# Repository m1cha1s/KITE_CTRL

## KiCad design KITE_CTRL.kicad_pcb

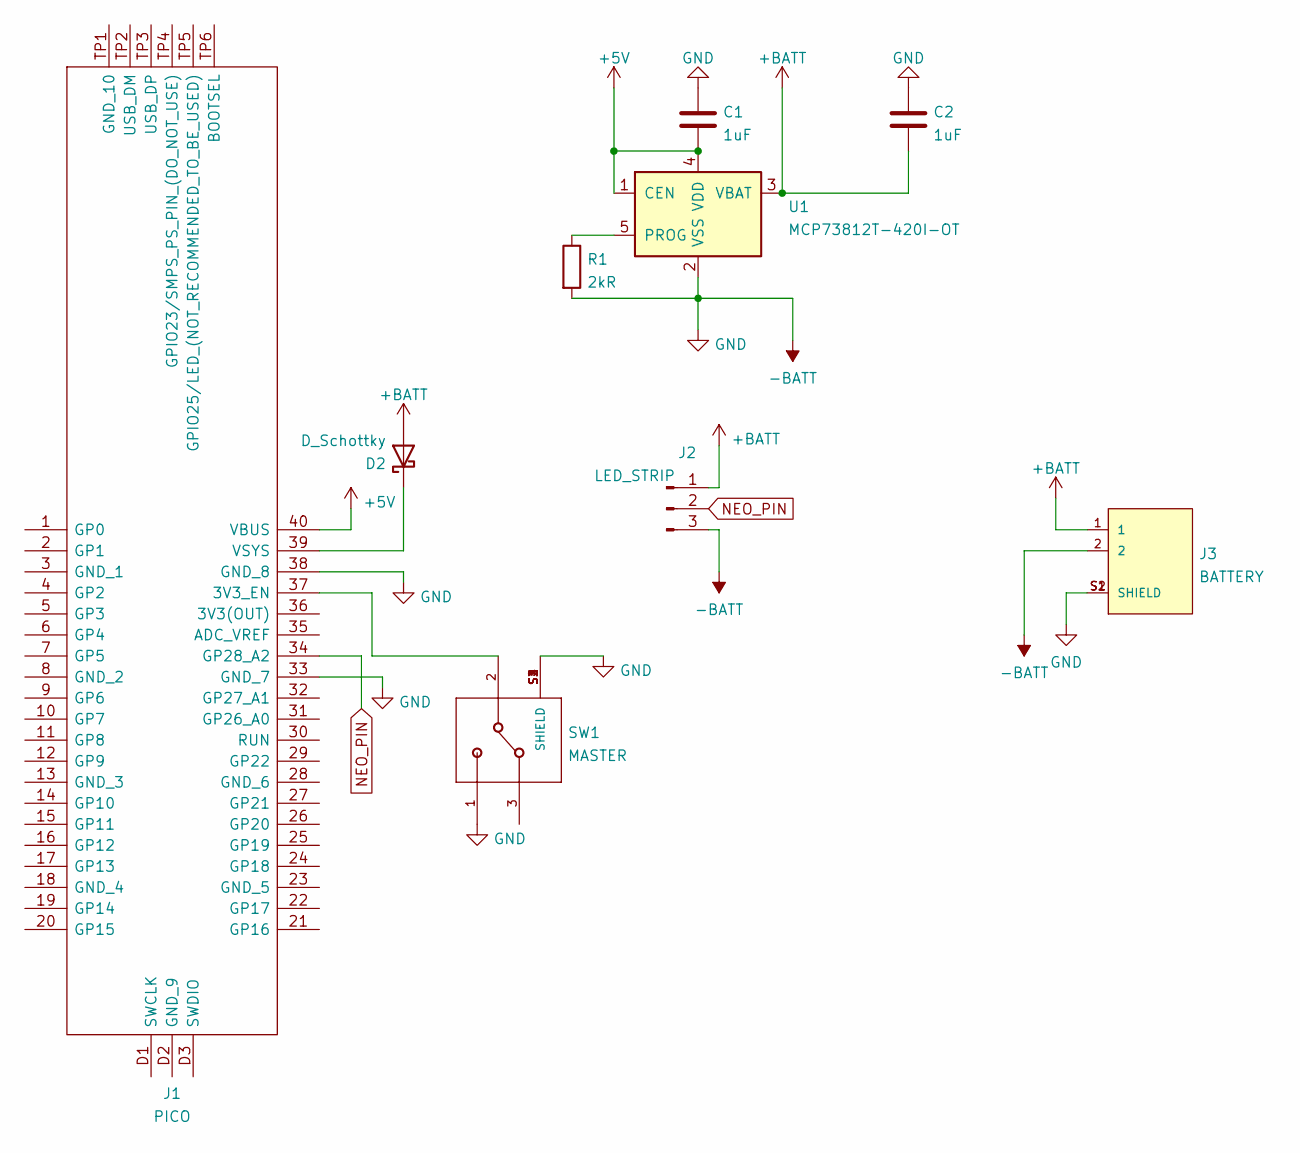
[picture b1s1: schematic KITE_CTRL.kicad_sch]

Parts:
C1, C2: 1uF; C_0402_1005Metric
D2: D_Schottky; D_0402_1005Metric
J1: PICO; Manufacturer_Part_Number PICO
J2: LED_STRIP; PinSocket_1x03_P2.54mm_Vertical
J3: BATTERY; JST_S2B-PH-SM4-TB(LF)(SN)
R1: 2kR; R_0402_1005Metric
SW1: MASTER; SW_PCM12SMTR
U1: MCP73812T-420I-OT; SOT-23-5

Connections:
+5V: C1.2, J1.40 (VBUS), U1.1 (CEN), U1.4 (VDD)
+BATT: C2.2, D2.2 (A), J2.1, J3.1, U1.3 (VBAT)
-BATT: C1.1, C2.1, J1.33 (GND_7), J1.38 (GND_8), J2.3, J3.2, J3.S1 (SHIELD), J3.S2 (SHIELD), R1.2, SW1.1, SW1.S1 (SHIELD), SW1.S2 (SHIELD), SW1.S3 (SHIELD), SW1.S4 (SHIELD), U1.2 (VSS)
NEO_PIN: J1.34 (GP28_A2), J2.2
unnamed: J1.37 (3V3_EN), SW1.2
unnamed: D2.1 (K), J1.39 (VSYS)
unnamed: R1.1, U1.5 (PROG)

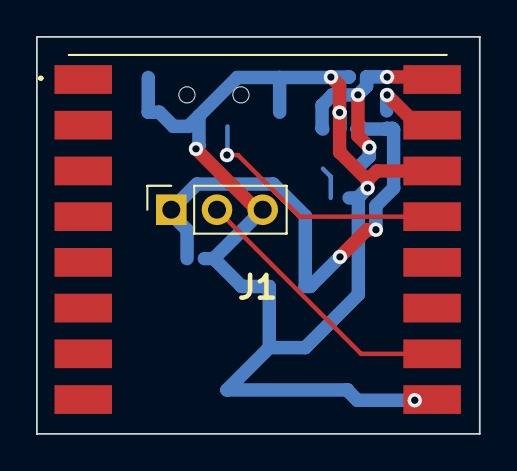
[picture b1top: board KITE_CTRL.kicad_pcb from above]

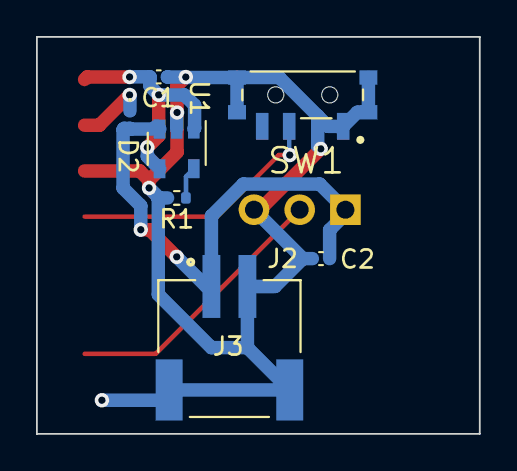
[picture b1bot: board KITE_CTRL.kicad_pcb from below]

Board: 2 copper layers, 24.6 x 22.1 mm, 9 parts (7 on the bottom side), 7 nets.

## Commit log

2021-09-18 Initial commit. Component selection phase.
2021-09-24 Selected battery charger
2021-09-30 Finnished making schematic moving on to making PCB
2021-09-30 Finnished laying out the board
